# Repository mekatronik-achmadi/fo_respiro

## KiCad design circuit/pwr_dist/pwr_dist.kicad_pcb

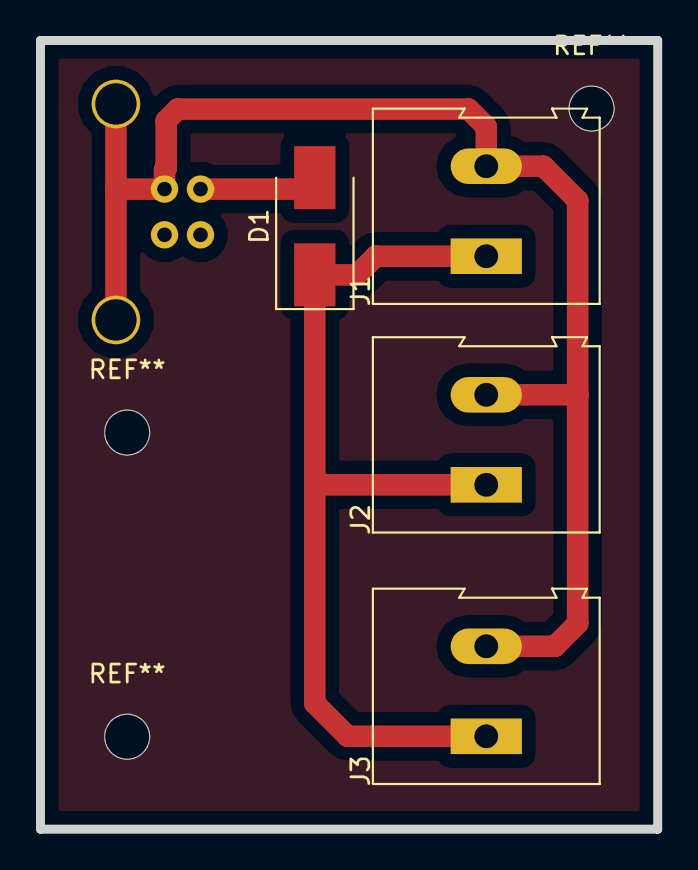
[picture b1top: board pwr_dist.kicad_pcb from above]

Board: 2 copper layers, 34.3 x 43.8 mm, 5 parts (1 on the bottom side), 3 nets.

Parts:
D1: D; D_SMB_Handsoldering
J1, J2, J3: CONN_01X02; AK300-2
USB1: USB_B

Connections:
GND: J1.2, J2.2, J3.2, USB1.4, USB1.5
unnamed: D1.1, J1.1, J2.1, J3.1
unnamed: D1.2, USB1.1

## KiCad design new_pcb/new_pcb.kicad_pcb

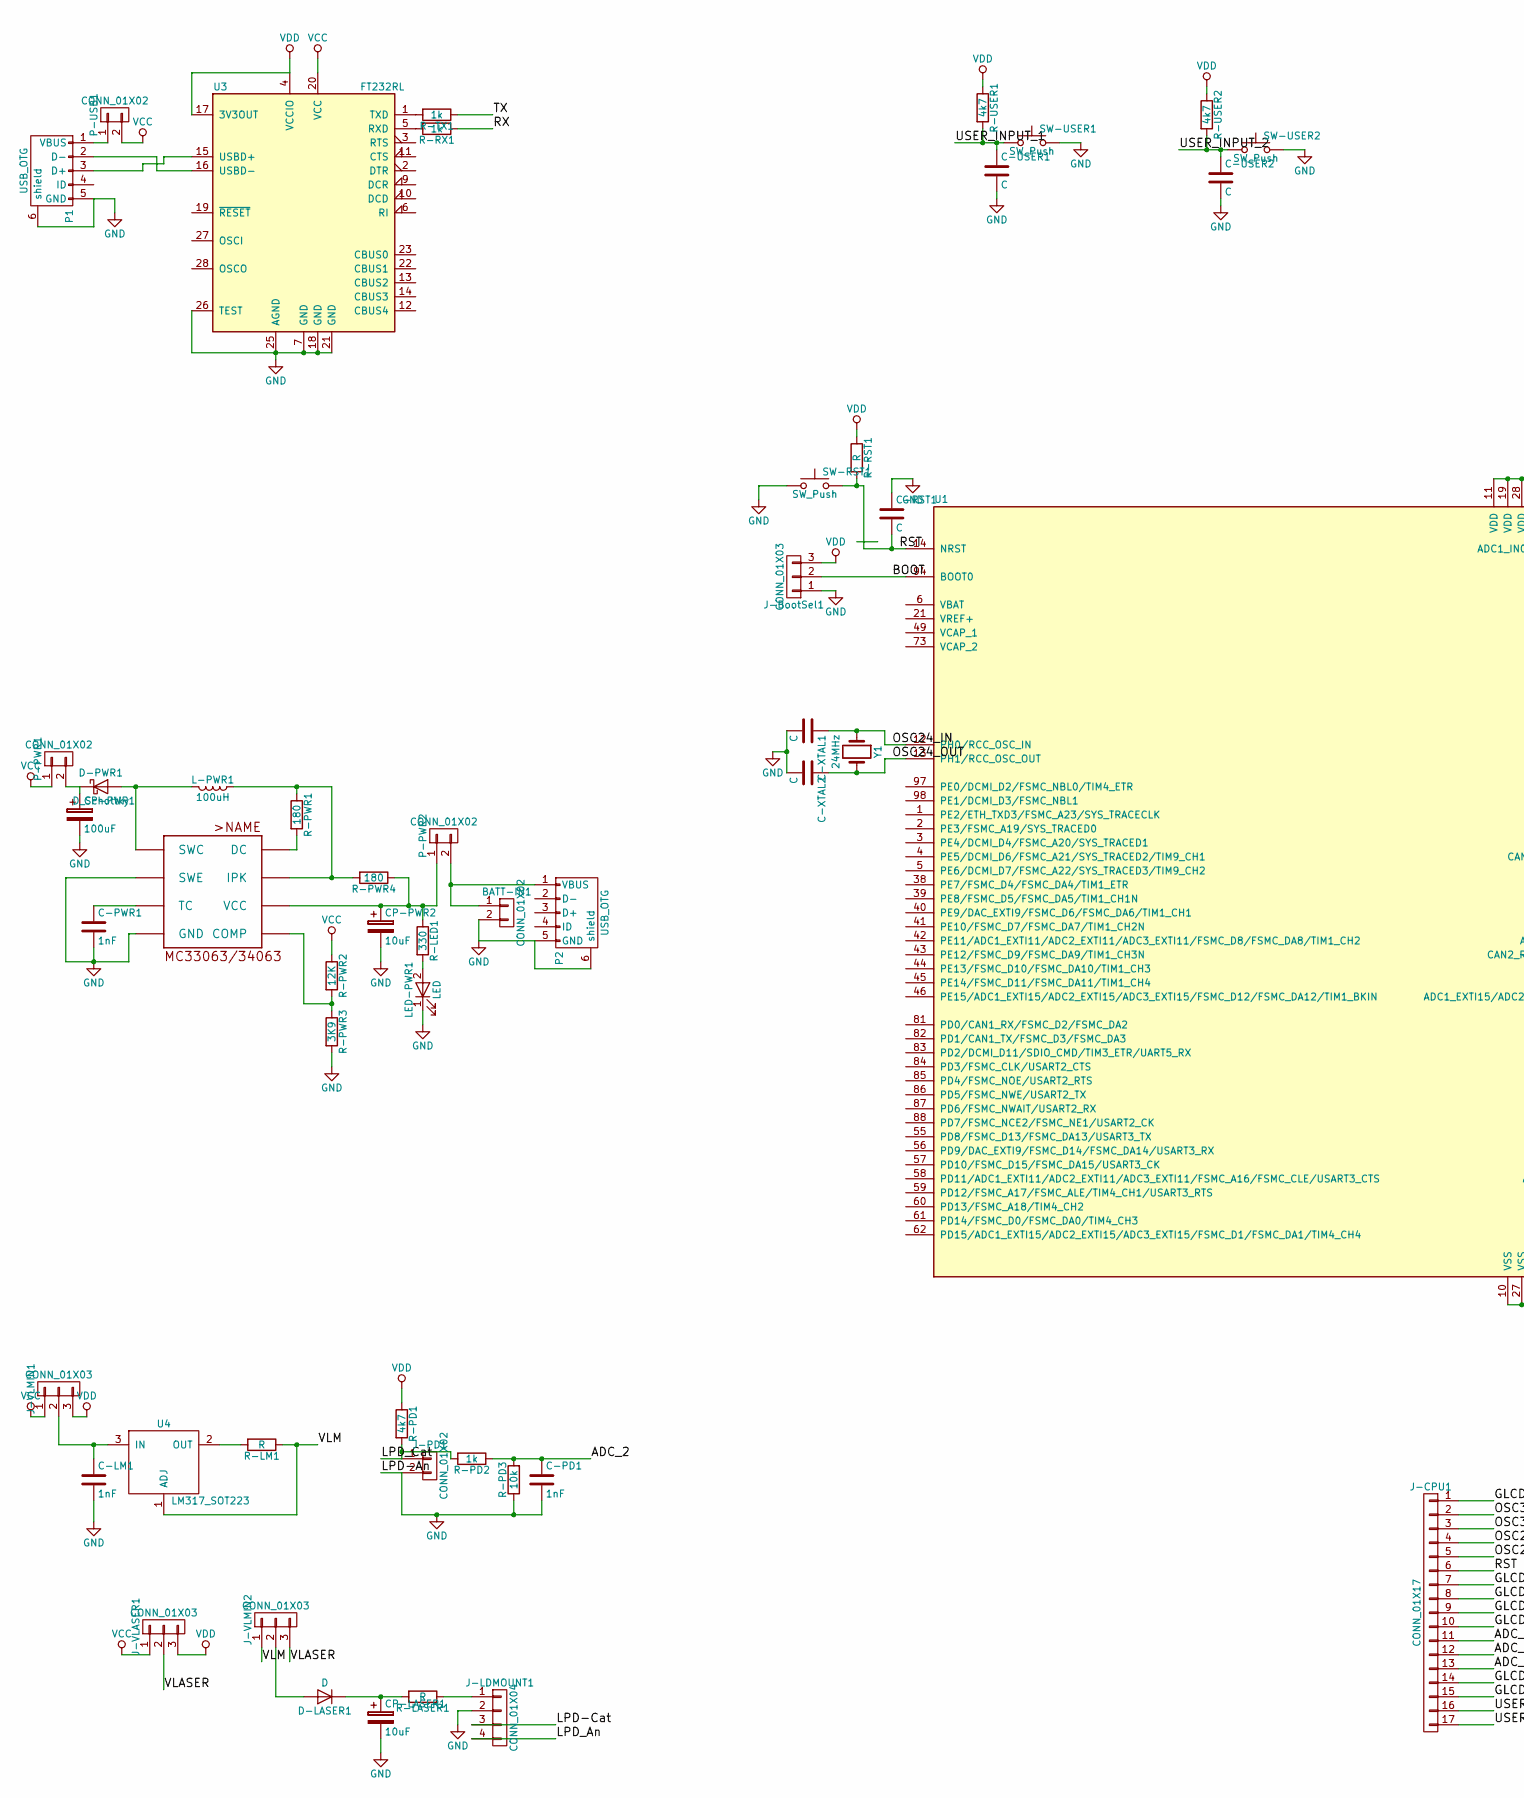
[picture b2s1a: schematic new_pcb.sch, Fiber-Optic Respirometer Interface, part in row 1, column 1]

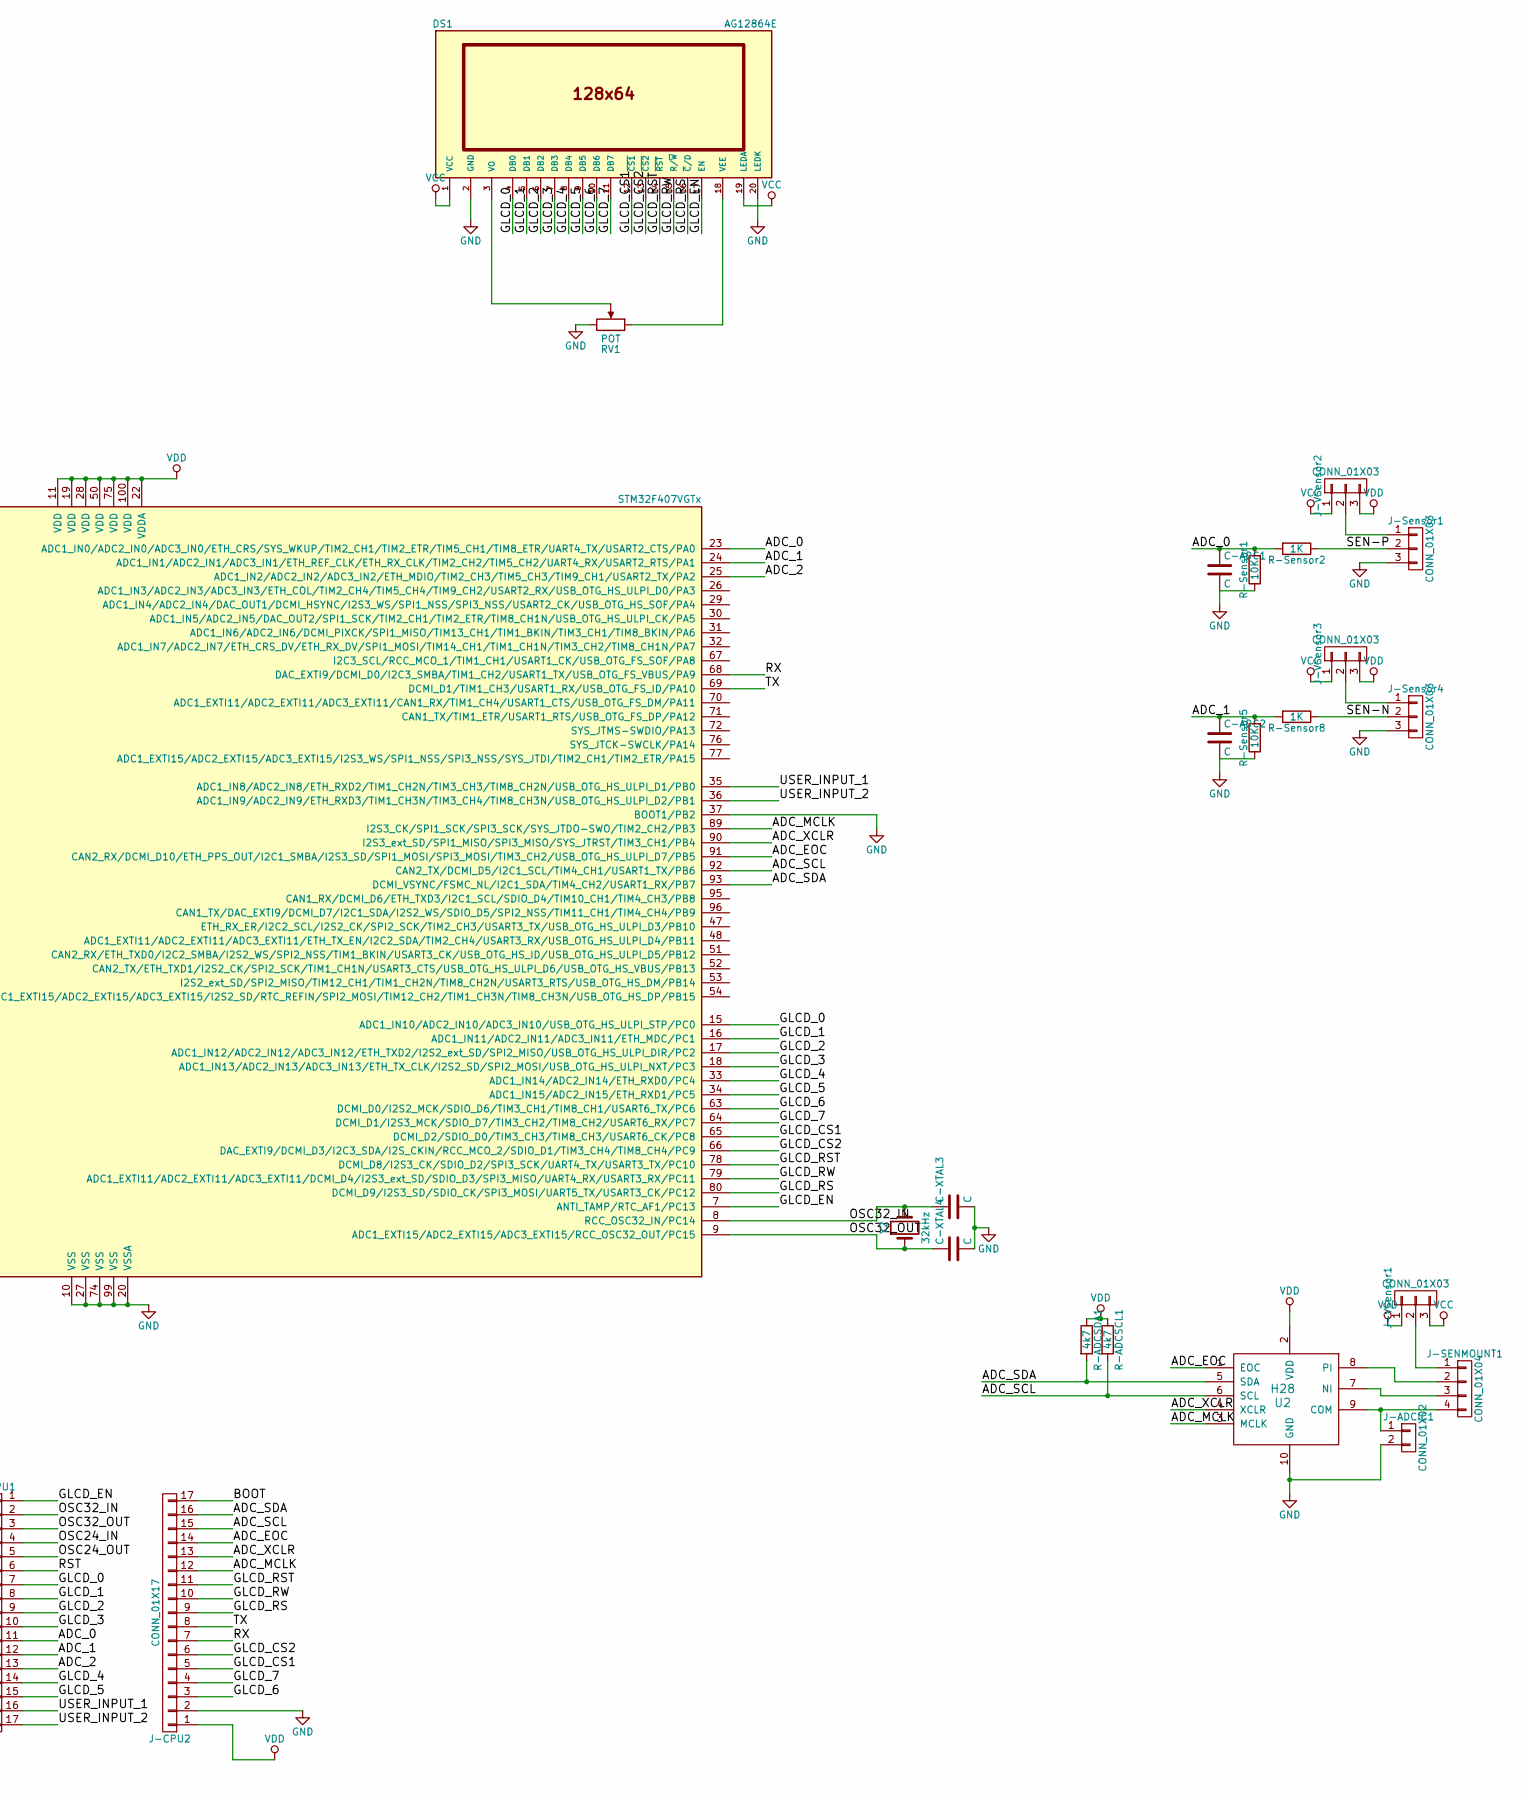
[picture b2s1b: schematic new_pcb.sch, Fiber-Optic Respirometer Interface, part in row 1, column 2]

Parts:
BATT-IN1: CONN_01X02; AK300-2
C-ADC1, C-ADC2: C; C_0805_HandSoldering
C-LM1: 1nF; C_0805_HandSoldering
C-PD1: 1nF; C_0805_HandSoldering
C-PWR1: 1nF; C_0805_HandSoldering
C-RST1: C; C_0805_HandSoldering
C-USER1, C-USER2: C; C_0805_HandSoldering
C-XTAL1, C-XTAL2, C-XTAL3, C-XTAL4: C; C_0805_HandSoldering
CP-LASER1: 10uF; CP_Elec_4x5.3
CP-PWR1: 100uF; CP_Elec_4x5.3
CP-PWR2: 10uF; CP_Elec_4x5.3
D-LASER1: D; D_SMB_Standard
D-PWR1: D_Schottky; D_SMB_Standard
DS1: AG12864E
J-ADCIC1: CONN_01X02; Pin_Header_Straight_1x02_Pitch2.54mm
J-BootSel1: CONN_01X03; Pin_Header_Straight_1x03_Pitch2.54mm
J-CPU1, J-CPU2: CONN_01X17; Pin_Header_Straight_1x17_Pitch2.54mm
J-LDMOUNT1: CONN_01X04; Pin_Header_Straight_1x04_Pitch2.54mm
J-PD1: CONN_01X02; Pin_Header_Straight_1x02_Pitch2.54mm
J-SENMOUNT1: CONN_01X04; Pin_Header_Straight_1x04_Pitch2.54mm
J-Sensor1, J-Sensor4: CONN_01X03; Pin_Header_Straight_1x03_Pitch2.54mm
J-VLASER1: CONN_01X03; Pin_Header_Straight_1x03_Pitch2.54mm
J-VLMIN1, J-VLMIN2: CONN_01X03; Pin_Header_Straight_1x03_Pitch2.54mm
J-VSensor1, J-VSensor2, J-VSensor3: CONN_01X03; Pin_Header_Straight_1x03_Pitch2.54mm
L-PWR1: 100uH; SELF-WE-PD-XXL
LED-PWR1: LED; LED_D3.0mm
P1, P2: USB_OTG; USB_Mini-B
P-PWR1: CONN_01X02; Pin_Header_Straight_1x02_Pitch2.54mm
P-PWR2: CONN_01X02; AK300-2
P-USB1: CONN_01X02; Pin_Header_Straight_1x02_Pitch2.54mm
R-ADCSCL1: 4k7; R_0805_HandSoldering
R-ADCSDA1: 4k7; R_0805_HandSoldering
R-LASER1: R; R_0805_HandSoldering
R-LED1: 330; R_0805_HandSoldering
R-LM1: R; R_0805_HandSoldering
R-PD1: 4k7; R_0805_HandSoldering
R-PD2: 1k; R_0805_HandSoldering
R-PD3: 10k; R_0805_HandSoldering
R-PWR1, R-PWR4: 180; R_0805_HandSoldering
R-PWR2: 12K; R_0805_HandSoldering
R-PWR3: 3K9; R_0805_HandSoldering
R-RST1: R; R_0805_HandSoldering
R-RX1: 1k; R_0805_HandSoldering
R-Sensor1, R-Sensor5: 10K; R_0805_HandSoldering
R-Sensor2, R-Sensor8: 1K; R_0805_HandSoldering
R-TX1: 1k; R_0805_HandSoldering
R-USER1, R-USER2: 4k7; R_0805_HandSoldering
RV1: POT; Potentiometer_Trimmer-EVM3E
SW-RST1: SW_Push; SW_PUSH-12mm
SW-USER1, SW-USER2: SW_Push; SW_PUSH-12mm
U1: STM32F407VGTx; LQFP-100_14x14mm_Pitch0.5mm
U2: H28; MSOP-10_3x3mm_Pitch0.5mm
U3: FT232RL; TSSOP-28_4.4x9.7mm_Pitch0.65mm
U4: LM317_SOT223; TO-252-2Lead
U-BATT1: MC33063/MC34063D_SO08; SOIC-8_3.9x4.9mm_Pitch1.27mm
Y1: 24MHz; Crystal_HC49-U_Horizontal
Y2: 32kHz; Crystal_Round_d3.0mm_Vertical

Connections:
/ADC_0: C-ADC1.1, J-CPU1.11, R-Sensor1.2, R-Sensor2.2, U1.23 (ADC1_IN0/ADC2_IN0/ADC3_IN0/ETH_CRS/SYS_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)
/ADC_1: C-ADC2.1, J-CPU1.12, R-Sensor5.2, R-Sensor8.2, U1.24 (ADC1_IN1/ADC2_IN1/ADC3_IN1/ETH_REF_CLK/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)
/ADC_2: C-PD1.1, J-CPU1.13, R-PD2.1, R-PD3.2, U1.25 (ADC1_IN2/ADC2_IN2/ADC3_IN2/ETH_MDIO/TIM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)
/ADC_EOC: J-CPU2.14, U1.91 (CAN2_RX/DCMI_D10/ETH_PPS_OUT/I2C1_SMBA/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), U2.1 (EOC)
/ADC_MCLK: J-CPU2.12, U1.89 (I2S3_CK/SPI1_SCK/SPI3_SCK/SYS_JTDO-SWO/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), U2.3 (MCLK)
/ADC_SCL: J-CPU2.15, R-ADCSCL1.2, U1.92 (CAN2_TX/DCMI_D5/I2C1_SCL/TIM4_CH1/USART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), U2.6 (SCL)
/ADC_SDA: J-CPU2.16, R-ADCSDA1.2, U1.93 (DCMI_VSYNC/FSMC_NL/I2C1_SDA/TIM4_CH2/US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), U2.5 (SDA)
/ADC_XCLR: J-CPU2.13, U1.90 (I2S3_ext_SD/SPI1_MISO/SPI3_MISO/SYS_JTR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), U2.4 (XCLR)
/BOOT: J-BootSel1.2, J-CPU2.17, U1.94 (BOOT0)
/GLCD_0: DS1.4 (DB0), J-CPU1.7, U1.15 (ADC1_IN10/ADC2_IN10/ADC3_IN10/USB_OTG_H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)
/GLCD_1: DS1.5 (DB1), J-CPU1.8, U1.16 (ADC1_IN11/ADC2_IN11/ADC3_IN11/ETH_MDC/P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)
/GLCD_2: DS1.6 (DB2), J-CPU1.9, U1.17 (ADC1_IN12/ADC2_IN12/ADC3_IN12/ETH_TXD2/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)
/GLCD_3: DS1.7 (DB3), J-CPU1.10, U1.18 (ADC1_IN13/ADC2_IN13/ADC3_IN13/ETH_TX_CL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)
/GLCD_4: DS1.8 (DB4), J-CPU1.14, U1.33 (ADC1_IN14/ADC2_IN14/ETH_RXD0/PC4)
/GLCD_5: DS1.9 (DB5), J-CPU1.15, U1.34 (ADC1_IN15/ADC2_IN15/ETH_RXD1/PC5)
/GLCD_6: DS1.10 (DB6), J-CPU2.3, U1.63 (DCMI_D0/I2S2_MCK/SDIO_D6/TIM3_CH1/TIM8_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)
/GLCD_7: DS1.11 (DB7), J-CPU2.4, U1.64 (DCMI_D1/I2S3_MCK/SDIO_D7/TIM3_CH2/TIM8_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)
/GLCD_CS1: DS1.12 (~CS1~), J-CPU2.5, U1.65 (DCMI_D2/SDIO_D0/TIM3_CH3/TIM8_CH3/USART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)
/GLCD_CS2: DS1.13 (~CS2~), J-CPU2.6, U1.66 (DAC_EXTI9/DCMI_D3/I2C3_SDA/I2S_CKIN/RCC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)
/GLCD_EN: DS1.17 (EN), J-CPU1.1, U1.7 (ANTI_TAMP/RTC_AF1/PC13)
/GLCD_RS: DS1.16 (~C~/D), J-CPU2.9, U1.80 (DCMI_D9/I2S3_SD/SDIO_CK/SPI3_MOSI/UART5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)
/GLCD_RST: DS1.14 (~RST~), J-CPU2.11, U1.78 (DCMI_D8/I2S3_CK/SDIO_D2/SPI3_SCK/UART4_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)
/GLCD_RW: DS1.15 (R/~W~), J-CPU2.10, U1.79 (ADC1_EXTI11/ADC2_EXTI11/ADC3_EXTI11/DCM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)
/LPD-Cat: J-LDMOUNT1.3
/LPD_An: J-LDMOUNT1.4
/LPD_Cat: J-PD1.1, R-PD1.2, R-PD2.2
/OSC24_IN: C-XTAL1.1, J-CPU1.4, U1.12 (PH0/RCC_OSC_IN), Y1.1
/OSC24_OUT: C-XTAL2.1, J-CPU1.5, U1.13 (PH1/RCC_OSC_OUT), Y1.2
/OSC32_IN: C-XTAL3.1, J-CPU1.2, U1.8 (RCC_OSC32_IN/PC14), Y2.2
/OSC32_OUT: C-XTAL4.1, J-CPU1.3, U1.9 (ADC1_EXTI15/ADC2_EXTI15/ADC3_EXTI15/RCC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), Y2.1
/RST: C-RST1.2, J-CPU1.6, R-RST1.2, SW-RST1.2, U1.14 (NRST)
/RX: J-CPU2.7, R-RX1.1, U1.68 (DAC_EXTI9/DCMI_D0/I2C3_SMBA/TIM1_CH2/US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)
/SEN-N: J-Sensor4.2, R-Sensor8.1
/SEN-P: J-Sensor1.2, R-Sensor2.1
/TX: J-CPU2.8, R-TX1.1, U1.69 (DCMI_D1/TIM1_CH3/USART1_RX/USB_OTG_FS_I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)
/USER_INPUT_1: C-USER1.1, J-CPU1.16, R-USER1.2, SW-USER1.1, U1.35 (ADC1_IN8/ADC2_IN8/ETH_RXD2/TIM1_CH2N/TI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)
/USER_INPUT_2: C-USER2.1, J-CPU1.17, R-USER2.2, SW-USER2.1, U1.36 (ADC1_IN9/ADC2_IN9/ETH_RXD3/TIM1_CH3N/TI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)
/VLASER: J-VLASER1.2, J-VLMIN2.3
/VLM: J-VLMIN2.1, R-LM1.1, U4.1 (ADJ)
GND: BATT-IN1.2, C-ADC1.2, C-ADC2.2, C-LM1.2, C-PD1.2, C-PWR1.2, C-RST1.1, C-USER1.2, C-USER2.2, C-XTAL1.2, C-XTAL2.2, C-XTAL3.2, C-XTAL4.2, CP-LASER1.2, CP-PWR1.2, CP-PWR2.2, DS1.2 (GND), DS1.20 (LEDK), J-ADCIC1.2, J-BootSel1.1, J-CPU2.2, J-LDMOUNT1.2, J-PD1.2, J-Sensor1.3, J-Sensor4.3, LED-PWR1.1 (K), P1.5 (GND), P1.6 (shield), P2.5 (GND), P2.6 (shield), R-PD3.1, R-PWR3.2, R-Sensor1.1, R-Sensor5.1, RV1.3, SW-RST1.1, SW-USER1.2, SW-USER2.2, U1.10 (VSS), U1.20 (VSSA), U1.27 (VSS), U1.37 (BOOT1/PB2), U1.74 (VSS), U1.99 (VSS), U2.10 (GND), U3.7 (GND), U3.18 (GND), U3.21 (GND), U3.25 (AGND), U3.26 (TEST), U-BATT1.2 (SWE), U-BATT1.4 (GND)
unnamed: BATT-IN1.1, P2.1 (VBUS), P-PWR2.2
unnamed: C-LM1.1, J-VLMIN1.2, U4.3 (IN)
unnamed: C-PWR1.1, U-BATT1.3 (TC)
unnamed: CP-LASER1.1, D-LASER1.1 (K), R-LASER1.2
unnamed: CP-PWR1.1, D-PWR1.1 (K), P-PWR1.2
unnamed: CP-PWR2.1, P-PWR2.1, R-LED1.1, R-PWR4.1, U-BATT1.6 (VCC)
unnamed: D-LASER1.2 (A), J-VLMIN2.2
unnamed: D-PWR1.2 (A), L-PWR1.2, U-BATT1.1 (SWC)
unnamed: DS1.3 (VO), RV1.2
unnamed: DS1.18 (VEE), RV1.1
unnamed: J-ADCIC1.1, J-SENMOUNT1.4, U2.9 (COM)
unnamed: J-LDMOUNT1.1, R-LASER1.1
unnamed: J-SENMOUNT1.1, J-VSensor1.2
unnamed: J-SENMOUNT1.2, U2.8 (PI)
unnamed: J-SENMOUNT1.3, U2.7 (NI)
unnamed: J-Sensor1.1, J-VSensor2.2
unnamed: J-Sensor4.1, J-VSensor3.2
unnamed: L-PWR1.1, R-PWR1.1, R-PWR4.2, U-BATT1.7 (IPK)
unnamed: LED-PWR1.2 (A), R-LED1.2
unnamed: P1.2 (D-), U3.16 (USBD-)
unnamed: P1.3 (D+), U3.15 (USBD+)
unnamed: P1.1 (VBUS), P-USB1.1
unnamed: R-LM1.2, U4.2 (OUT)
unnamed: R-PWR1.2, U-BATT1.8 (DC)
unnamed: R-PWR2.2, R-PWR3.1, U-BATT1.5 (COMP)
unnamed: R-RX1.2, U3.5 (RXD)
unnamed: R-TX1.2, U3.1 (TXD)
VCC: DS1.1 (VCC), DS1.19 (LEDA), J-VLASER1.1, J-VLMIN1.1, J-VSensor1.3, J-VSensor2.1, J-VSensor3.1, P-PWR1.1, P-USB1.2, R-PWR2.1, U3.20 (VCC)
VDD: J-BootSel1.3, J-CPU2.1, J-VLASER1.3, J-VLMIN1.3, J-VSensor1.1, J-VSensor2.3, J-VSensor3.3, R-ADCSCL1.1, R-ADCSDA1.1, R-PD1.1, R-RST1.1, R-USER1.1, R-USER2.1, U1.11 (VDD), U1.19 (VDD), U1.22 (VDDA), U1.28 (VDD), U1.50 (VDD), U1.75 (VDD), U1.100 (VDD), U2.2 (VDD), U3.4 (VCCIO), U3.17 (3V3OUT)

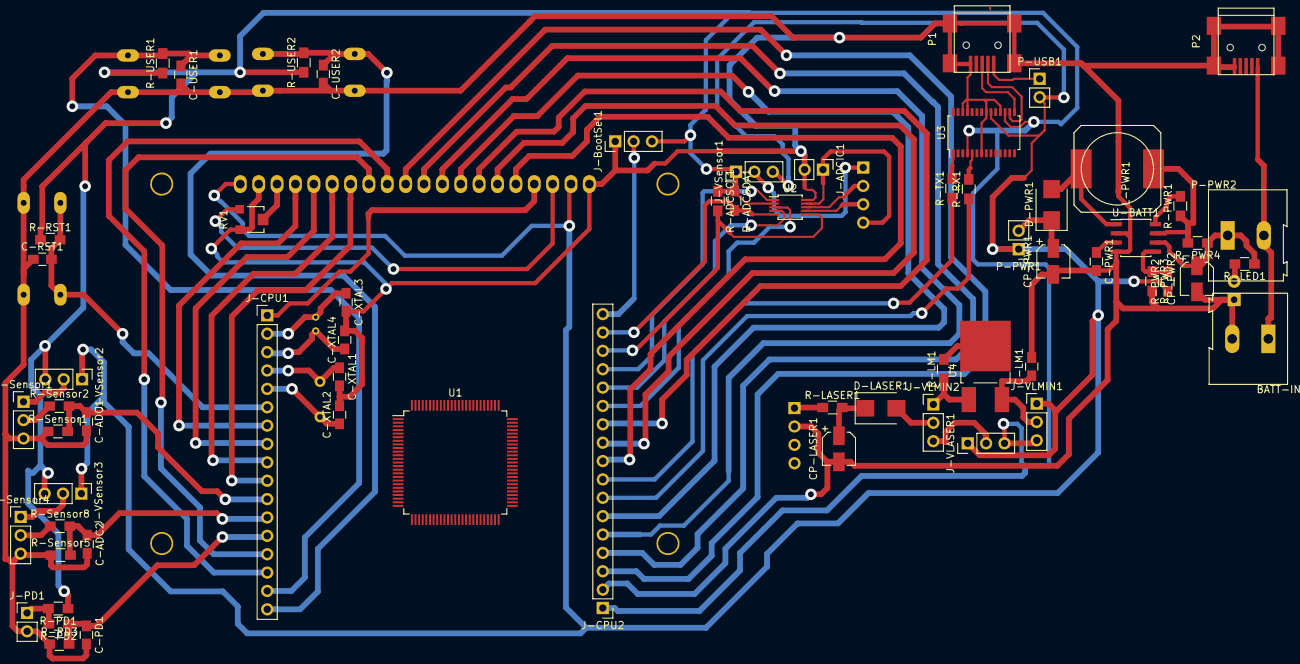
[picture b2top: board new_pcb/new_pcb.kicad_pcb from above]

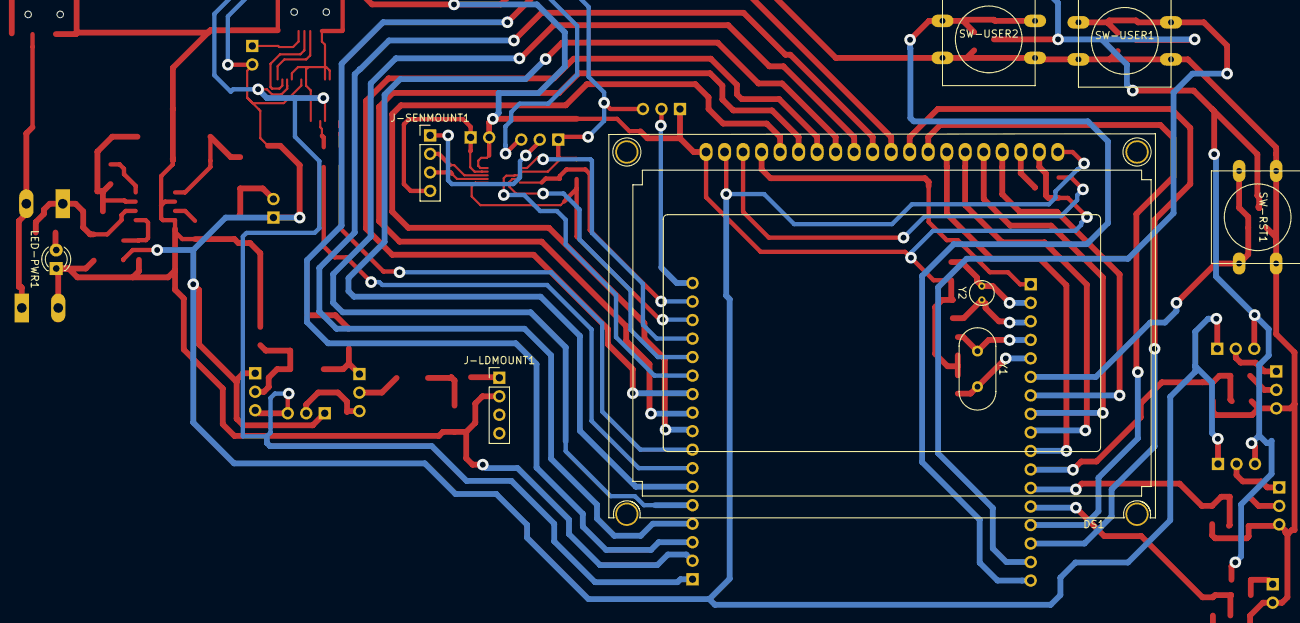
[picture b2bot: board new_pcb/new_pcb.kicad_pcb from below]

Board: 2 copper layers, 73 parts (9 on the bottom side), 67 nets.

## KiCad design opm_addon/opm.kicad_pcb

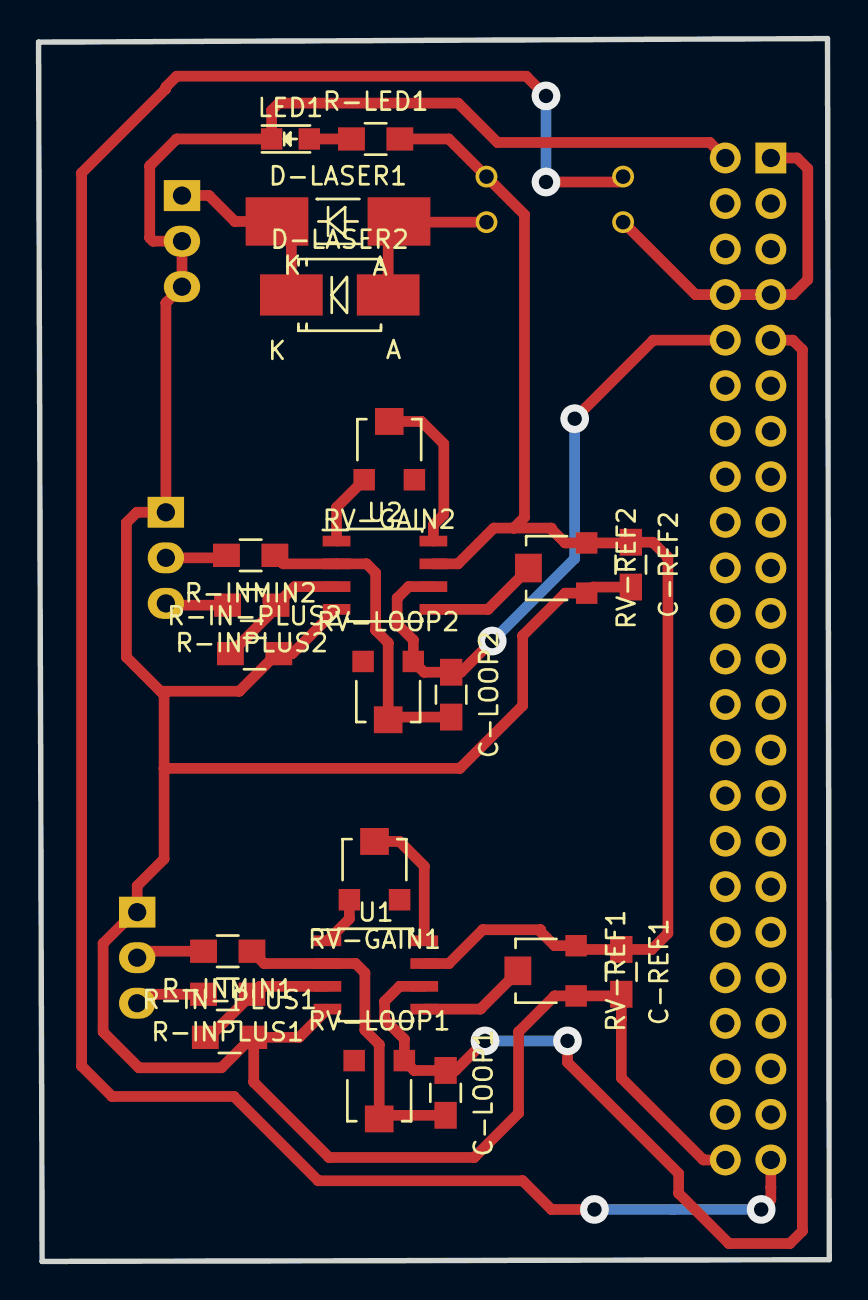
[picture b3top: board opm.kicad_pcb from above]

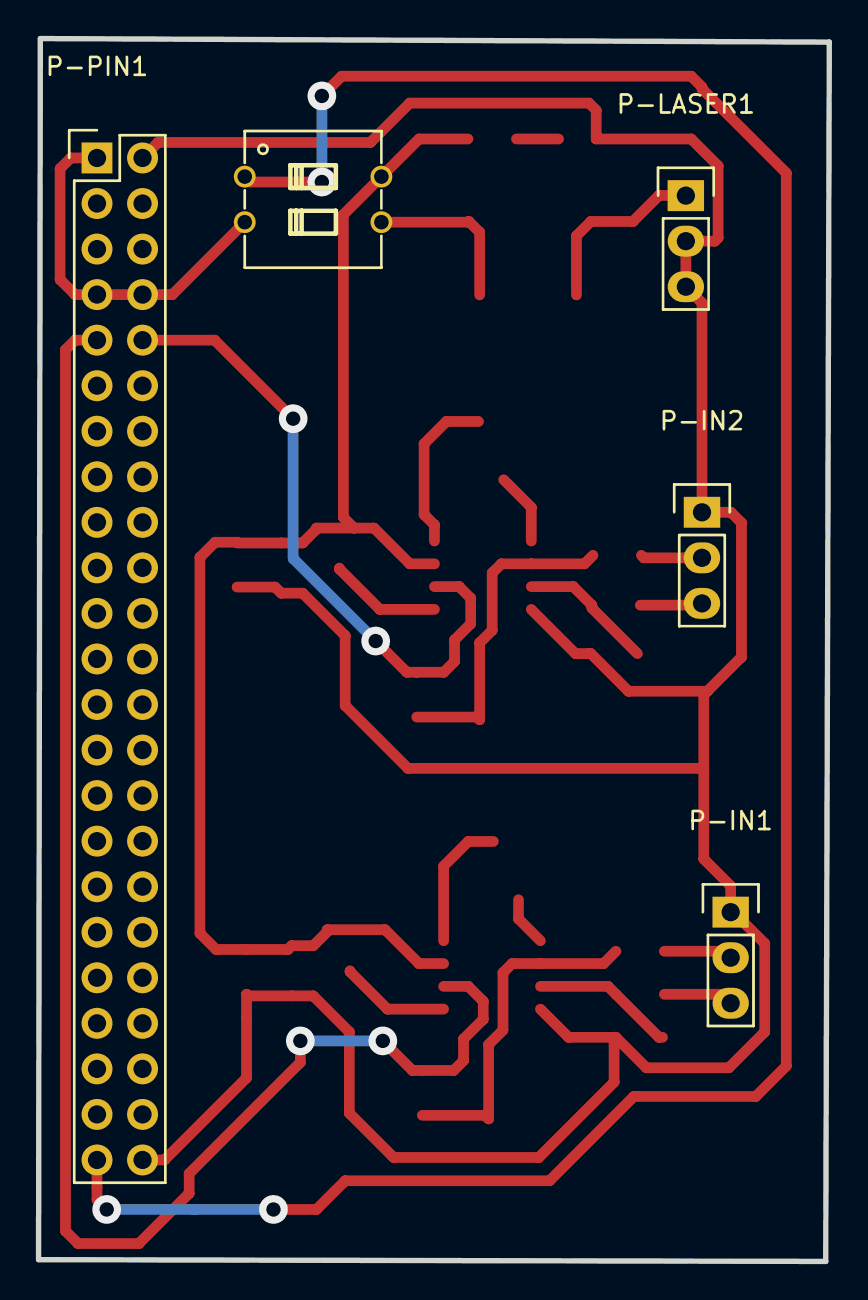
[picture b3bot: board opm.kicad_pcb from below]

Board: 2 copper layers, 44.1 x 68.2 mm, 27 parts (5 on the bottom side), 23 nets.

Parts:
C-LOOP1, C-LOOP2: 0.1uF; C_0805_HandSoldering
C-REF1, C-REF2: 0.1uF; C_0805_HandSoldering
D-LASER1: D; MELF_Handsoldering
D-LASER2: D; SMB_Handsoldering
LED1: LED; LED_0805
P-IN1, P-IN2: CONN_01X03; Pin_Header_Straight_1x03
P-LASER1: CONN_01X03; Pin_Header_Straight_1x03
P-PIN1: CONN_02X23; Pin_Header_Straight_2x23
R-IN-PLUS1, R-IN-PLUS2: 100K; R_0805_HandSoldering
R-INMIN1, R-INMIN2: 100K; R_0805_HandSoldering
R-INPLUS1, R-INPLUS2: 100K; R_0805_HandSoldering
R-LED1: 330; R_0805_HandSoldering
RV-GAIN1, RV-GAIN2: 100K; Potentiometer_Trimmer-EVM3E
RV-LOOP1, RV-LOOP2: 100K; Potentiometer_Trimmer-EVM3E
RV-REF1, RV-REF2: 100K; Potentiometer_Trimmer-EVM3E
SW-PWR1: SW_DIP_x02; DIP02YL
U1, U2: AD620; SOIC-8_3.9x4.9mm_Pitch1.27mm

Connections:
/ADC0: C-LOOP2.1, P-PIN1.10, RV-LOOP2.1, U2.6
/ADC1: C-LOOP1.1, P-PIN1.9, RV-LOOP1.1, U1.6
/PIN_VCC: P-PIN1.45, SW-PWR1.1
/PIN_VDD: P-PIN1.1, P-PIN1.7, P-PIN1.8, SW-PWR1.2
GND: C-REF1.2, C-REF2.2, LED1.1, P-IN1.1, P-IN2.1, P-LASER1.2, P-LASER1.3, P-PIN1.2, P-PIN1.46, R-IN-PLUS1.2, R-IN-PLUS2.2, RV-REF1.1, RV-REF2.1, U1.4, U2.4
unnamed: C-LOOP1.2, R-INMIN1.1, RV-LOOP1.2, U1.2
unnamed: C-LOOP2.2, R-INMIN2.1, RV-LOOP2.2, U2.2
unnamed: D-LASER1.1, D-LASER2.1, P-LASER1.1
unnamed: D-LASER1.2, D-LASER2.2, SW-PWR1.3
unnamed: LED1.2, R-LED1.1
unnamed: P-IN1.2, R-INMIN1.2
unnamed: P-IN1.3, R-INPLUS1.2
unnamed: P-IN2.2, R-INMIN2.2
unnamed: P-IN2.3, R-INPLUS2.2
unnamed: R-IN-PLUS1.1, R-INPLUS1.1, U1.3
unnamed: R-IN-PLUS2.1, R-INPLUS2.1, U2.3
unnamed: RV-GAIN1.1, U1.1
unnamed: RV-GAIN1.2, U1.8
unnamed: RV-GAIN2.1, U2.1
unnamed: RV-GAIN2.2, U2.8
unnamed: RV-REF1.2, U1.5
unnamed: RV-REF2.2, U2.5
VCC: C-REF1.1, C-REF2.1, R-LED1.2, RV-REF1.3, RV-REF2.3, SW-PWR1.4, U1.7, U2.7

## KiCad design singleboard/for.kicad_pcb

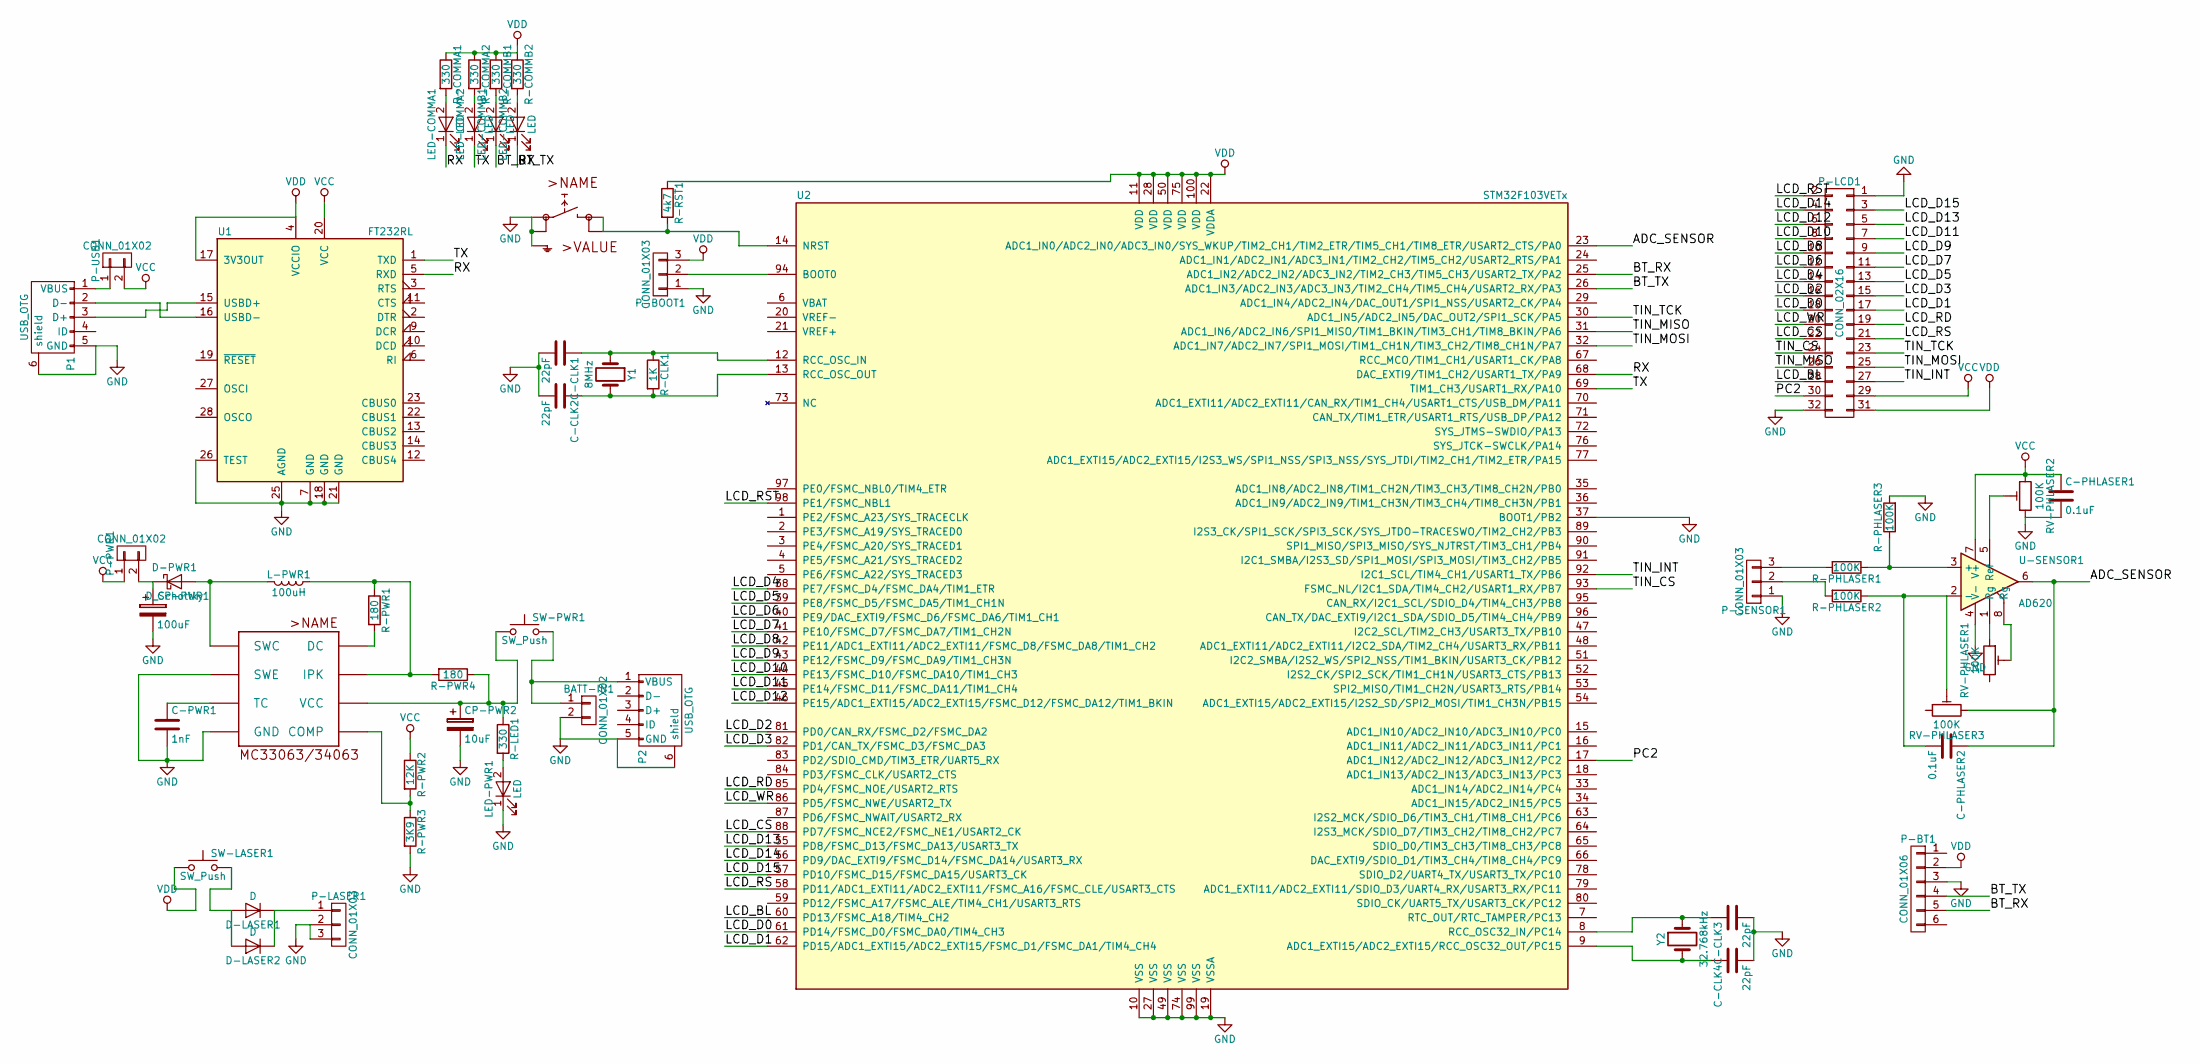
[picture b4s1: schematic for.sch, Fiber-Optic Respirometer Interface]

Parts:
BATT-IN1: CONN_01X02; AK300-2
C-CLK1, C-CLK2, C-CLK3, C-CLK4: 22pF; C_0805_HandSoldering
C-PHLASER1, C-PHLASER2: 0.1uF; C_0805_HandSoldering
C-PWR1: 1nF; C_0805_HandSoldering
CP-PWR1: 100uF; c_elec_4x5.3
CP-PWR2: 10uF; c_elec_4x5.3
D-LASER1: D; SMB_Standard
D-LASER2: D; MELF_Handsoldering
D-PWR1: D_Schottky; SMB_Standard
L-PWR1: 100uH; SELF-WE-PD-XXL
LED-COMMA1, LED-COMMA2: LED; LED_0805
LED-COMMB1, LED-COMMB2: LED; LED_0805
LED-PWR1: LED; LED_0805
P1, P2: USB_OTG; USB_Mini-B
P-BOOT1: CONN_01X03; Pin_Header_Straight_1x03
P-BT1: CONN_01X06; Pin_Header_Straight_1x06
P-LASER1: CONN_01X03; Pin_Header_Straight_1x03
P-LCD1: CONN_02X16; Pin_Header_Straight_2x16
P-PWR1: CONN_01X02; Pin_Header_Straight_1x02
P-SENSOR1: CONN_01X03; Pin_Header_Straight_1x03
P-USB1: CONN_01X02; Pin_Header_Straight_1x02
R-CLK1: 1K; R_0805_HandSoldering
R-COMMA1, R-COMMA2: 330; R_0805_HandSoldering
R-COMMB1, R-COMMB2: 330; R_0805_HandSoldering
R-LED1: 330; R_0805_HandSoldering
R-PHLASER1, R-PHLASER2, R-PHLASER3: 100K; R_0805_HandSoldering
R-PWR1, R-PWR4: 180; R_0805_HandSoldering
R-PWR2: 12K; R_0805_HandSoldering
R-PWR3: 3K9; R_0805_HandSoldering
R-RST1: 4k7; R_0805_HandSoldering
RV-PHLASER1, RV-PHLASER2, RV-PHLASER3: 100K; Potentiometer_Trimmer-EVM3E
SW-LASER1: SW_Push; AK300-2
SW-PWR1: SW_Push; AK300-2
U1: FT232RL; TSSOP-28_4.4x9.7mm_Pitch0.65mm
U2: STM32F103VETx; LQFP-100_14x14mm_Pitch0.5mm
U5: SKHMP*E010_SKHMPXE010; SKHMPXE010
U-BATT1: MC33063/MC34063D_SO08; SOIC-8_3.9x4.9mm_Pitch1.27mm
U-SENSOR1: AD620; SOIC-8_3.9x4.9mm_Pitch1.27mm
Y1: 8MHz; HC-49V
Y2: 32.768kHz; Crystal_Round_Horizontal_3mm

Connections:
/ADC_SENSOR: C-PHLASER2.1, RV-PHLASER3.3, U2.23 (ADC1_IN0/ADC2_IN0/ADC3_IN0/SYS_WKUP/TIM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), U-SENSOR1.6
/BT_RX: LED-COMMB1.1 (K), P-BT1.5, U2.25 (ADC1_IN2/ADC2_IN2/ADC3_IN2/TIM2_CH3/TIM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)
/BT_TX: LED-COMMB2.1 (K), P-BT1.4, U2.26 (ADC1_IN3/ADC2_IN3/ADC3_IN3/TIM2_CH4/TIM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)
/LCD_BL: P-LCD1.28, U2.60 (PD13/FSMC_A18/TIM4_CH2)
/LCD_CS: P-LCD1.22, U2.88 (PD7/FSMC_NCE2/FSMC_NE1/USART2_CK)
/LCD_D0: P-LCD1.18, U2.61 (PD14/FSMC_D0/FSMC_DA0/TIM4_CH3)
/LCD_D1: P-LCD1.17, U2.62 (PD15/ADC1_EXTI15/ADC2_EXTI15/FSMC_D1/FS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)
/LCD_D2: P-LCD1.16, U2.81 (PD0/CAN_RX/FSMC_D2/FSMC_DA2)
/LCD_D3: P-LCD1.15, U2.82 (PD1/CAN_TX/FSMC_D3/FSMC_DA3)
/LCD_D4: P-LCD1.14, U2.38 (PE7/FSMC_D4/FSMC_DA4/TIM1_ETR)
/LCD_D5: P-LCD1.13, U2.39 (PE8/FSMC_D5/FSMC_DA5/TIM1_CH1N)
/LCD_D6: P-LCD1.12, U2.40 (PE9/DAC_EXTI9/FSMC_D6/FSMC_DA6/TIM1_CH1)
/LCD_D7: P-LCD1.11, U2.41 (PE10/FSMC_D7/FSMC_DA7/TIM1_CH2N)
/LCD_D8: P-LCD1.10, U2.42 (PE11/ADC1_EXTI11/ADC2_EXTI11/FSMC_D8/FS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)
/LCD_D9: P-LCD1.9, U2.43 (PE12/FSMC_D9/FSMC_DA9/TIM1_CH3N)
/LCD_D10: P-LCD1.8, U2.44 (PE13/FSMC_D10/FSMC_DA10/TIM1_CH3)
/LCD_D11: P-LCD1.7, U2.45 (PE14/FSMC_D11/FSMC_DA11/TIM1_CH4)
/LCD_D12: P-LCD1.6, U2.46 (PE15/ADC1_EXTI15/ADC2_EXTI15/FSMC_D12/F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)
/LCD_D13: P-LCD1.5, U2.55 (PD8/FSMC_D13/FSMC_DA13/USART3_TX)
/LCD_D14: P-LCD1.4, U2.56 (PD9/DAC_EXTI9/FSMC_D14/FSMC_DA14/USART3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)
/LCD_D15: P-LCD1.3, U2.57 (PD10/FSMC_D15/FSMC_DA15/USART3_CK)
/LCD_RD: P-LCD1.19, U2.85 (PD4/FSMC_NOE/USART2_RTS)
/LCD_RS: P-LCD1.21, U2.58 (PD11/ADC1_EXTI11/ADC2_EXTI11/FSMC_A16/F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)
/LCD_RST: P-LCD1.2, U2.98 (PE1/FSMC_NBL1)
/LCD_WR: P-LCD1.20, U2.86 (PD5/FSMC_NWE/USART2_TX)
/PC2: P-LCD1.30, U2.17 (ADC1_IN12/ADC2_IN12/ADC3_IN12/PC2)
/RX: LED-COMMA1.1 (K), U1.5 (RXD), U2.68 (DAC_EXTI9/TIM1_CH2/USART1_TX/PA9)
/TIN_CS: P-LCD1.24, U2.93 (FSMC_NL/I2C1_SDA/TIM4_CH2/USART1_RX/PB7)
/TIN_INT: P-LCD1.27, U2.92 (I2C1_SCL/TIM4_CH1/USART1_TX/PB6)
/TIN_MISO: P-LCD1.26, U2.31 (ADC1_IN6/ADC2_IN6/SPI1_MISO/TIM1_BKIN/T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)
/TIN_MOSI: P-LCD1.25, U2.32 (ADC1_IN7/ADC2_IN7/SPI1_MOSI/TIM1_CH1N/T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)
/TIN_TCK: P-LCD1.23, U2.30 (ADC1_IN5/ADC2_IN5/DAC_OUT2/SPI1_SCK/PA5)
/TX: LED-COMMA2.1 (K), U1.1 (TXD), U2.69 (TIM1_CH3/USART1_RX/PA10)
GND: BATT-IN1.2, C-CLK1.2, C-CLK2.2, C-CLK3.2, C-CLK4.2, C-PHLASER1.2, C-PWR1.2, CP-PWR1.2, CP-PWR2.2, LED-PWR1.1 (K), P1.5 (GND), P1.6 (shield), P2.5 (GND), P2.6 (shield), P-BOOT1.1, P-BT1.3, P-LASER1.2, P-LASER1.3, P-LCD1.1, P-LCD1.32, P-SENSOR1.1, R-PHLASER3.2, R-PWR3.2, RV-PHLASER2.1, U1.7 (GND), U1.18 (GND), U1.21 (GND), U1.25 (AGND), U1.26 (TEST), U2.10 (VSS), U2.19 (VSSA), U2.27 (VSS), U2.37 (BOOT1/PB2), U2.49 (VSS), U2.74 (VSS), U2.99 (VSS), U5.1 (1.1), U5.2 (1.2), U5.5 (SH), U-BATT1.2 (SWE), U-BATT1.4 (GND), U-SENSOR1.4 (V-)
unnamed: BATT-IN1.1, P2.1 (VBUS), SW-PWR1.2
unnamed: C-CLK1.1, R-CLK1.1, U2.12 (RCC_OSC_IN), Y1.1
unnamed: C-CLK2.1, R-CLK1.2, U2.13 (RCC_OSC_OUT), Y1.2
unnamed: C-CLK3.1, U2.8 (RCC_OSC32_IN/PC14), Y2.1
unnamed: C-CLK4.1, U2.9 (ADC1_EXTI15/ADC2_EXTI15/RCC_OSC32_OUT/P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), Y2.2
unnamed: C-PHLASER2.2, R-PHLASER2.1, RV-PHLASER3.2, U-SENSOR1.2 (-)
unnamed: C-PWR1.1, U-BATT1.3 (TC)
unnamed: CP-PWR1.1, D-PWR1.1 (K), P-PWR1.2
unnamed: CP-PWR2.1, R-LED1.1, R-PWR4.1, SW-PWR1.1, U-BATT1.6 (VCC)
unnamed: D-LASER1.1 (K), D-LASER2.1 (K), P-LASER1.1
unnamed: D-LASER1.2 (A), D-LASER2.2 (A), SW-LASER1.2
unnamed: D-PWR1.2 (A), L-PWR1.2, U-BATT1.1 (SWC)
unnamed: L-PWR1.1, R-PWR1.1, R-PWR4.2, U-BATT1.7 (IPK)
unnamed: LED-COMMA1.2 (A), R-COMMA1.2
unnamed: LED-COMMA2.2 (A), R-COMMA2.2
unnamed: LED-COMMB1.2 (A), R-COMMB1.2
unnamed: LED-COMMB2.2 (A), R-COMMB2.2
unnamed: LED-PWR1.2 (A), R-LED1.2
unnamed: P1.2 (D-), U1.16 (USBD-)
unnamed: P1.3 (D+), U1.15 (USBD+)
unnamed: P-BOOT1.2, U2.94 (BOOT0)
unnamed: P-SENSOR1.2, R-PHLASER2.2
unnamed: P-SENSOR1.3, R-PHLASER1.2
unnamed: P1.1 (VBUS), P-USB1.1
unnamed: R-PHLASER1.1, R-PHLASER3.1, U-SENSOR1.3 (+)
unnamed: R-PWR1.2, U-BATT1.8 (DC)
unnamed: R-PWR2.2, R-PWR3.1, U-BATT1.5 (COMP)
unnamed: R-RST1.2, U2.14 (NRST), U5.3 (2.1), U5.4 (2.2)
unnamed: RV-PHLASER1.1, U-SENSOR1.1 (Rg)
unnamed: RV-PHLASER1.2, U-SENSOR1.8 (Rg)
unnamed: RV-PHLASER2.2, U-SENSOR1.5 (Ref)
VCC: C-PHLASER1.1, P-LCD1.29, P-PWR1.1, P-USB1.2, R-PWR2.1, RV-PHLASER2.3, U1.20 (VCC), U-SENSOR1.7 (V+)
VDD: P-BOOT1.3, P-BT1.2, P-LCD1.31, R-COMMA1.1, R-COMMA2.1, R-COMMB1.1, R-COMMB2.1, R-RST1.1, SW-LASER1.1, U1.4 (VCCIO), U1.17 (3V3OUT), U2.11 (VDD), U2.22 (VDDA), U2.28 (VDD), U2.50 (VDD), U2.75 (VDD), U2.100 (VDD)
